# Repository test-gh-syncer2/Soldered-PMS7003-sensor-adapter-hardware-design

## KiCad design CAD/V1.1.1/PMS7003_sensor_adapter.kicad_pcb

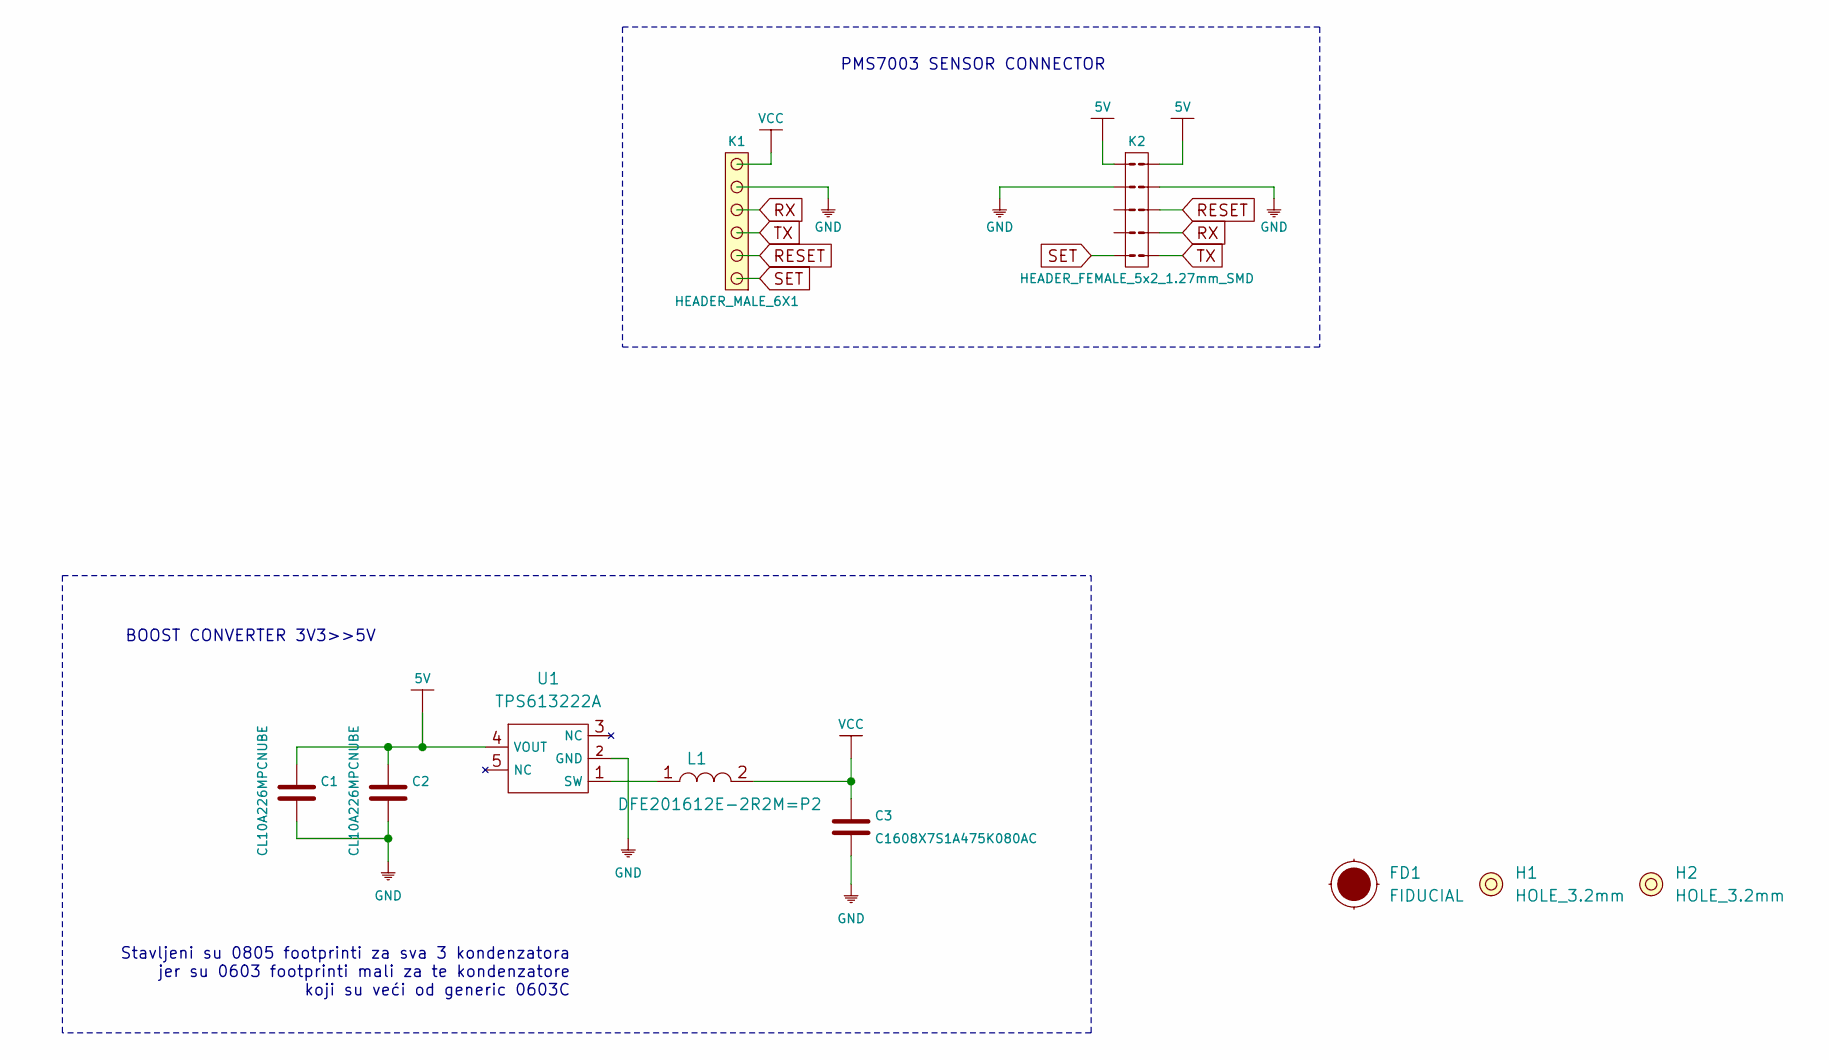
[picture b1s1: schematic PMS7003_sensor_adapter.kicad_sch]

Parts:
C1, C2: CL10A226MPCNUBE; 0805C
C3: C1608X7S1A475K080AC; 0805C
FD1: FIDUCIAL; FIDUCIAL_23
H1, H2: HOLE_3.2mm
K1: HEADER_MALE_6X1
K2: HEADER_FEMALE_5x2_1.27mm_SMD
L1: DFE201612E-2R2M=P2; 0806L
U1: TPS613222A; tps613222a

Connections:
5V: C1.2, C2.2, K2.1, K2.10, U1.4 (VOUT)
GND: C1.1, C2.1, C3.1, K1.5, K2.2, K2.9, U1.2 (GND)
unnamed: L1.1, U1.1 (SW)
RESET: K1.2, K2.8
RX: K1.4, K2.7
SET: K1.1, K2.5
TX: K1.3, K2.6
VCC: C3.2, K1.6, L1.2

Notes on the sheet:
BOOST CONVERTER 3V3>>5V
Stavljeni su 0805 footprinti za sva 3 kondenzatora jer su 0603 footprinti mali za te kondenzatore koji su veći od generic 0603C
PMS7003 SENSOR CONNECTOR

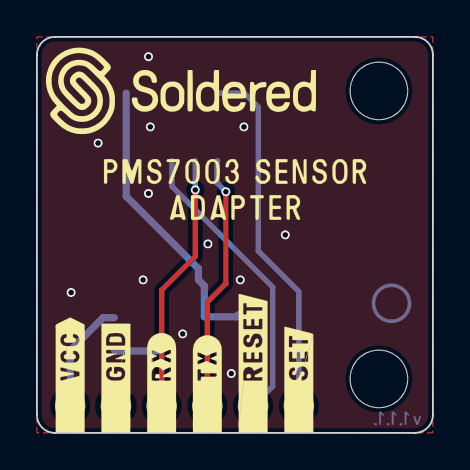
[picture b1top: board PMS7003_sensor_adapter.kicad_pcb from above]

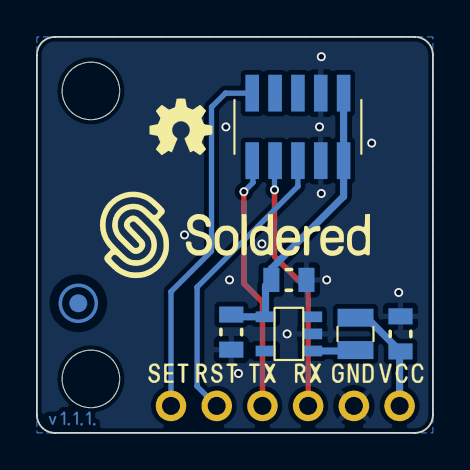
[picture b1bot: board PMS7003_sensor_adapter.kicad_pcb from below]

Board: 2 copper layers, 22.0 x 22.0 mm, 10 parts (7 on the bottom side), 8 nets.

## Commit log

2021-09-23 Syncing to git
2021-09-23 Updating open source files.
